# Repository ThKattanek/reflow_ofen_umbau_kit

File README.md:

# Reflow Ofen Umbau Kit
Mit dem „Reflow Ofen Umbau Kit“ (in Zukunft „Kit“ genannt) kann man einen alten Pizza Ofen zu einem Reflow Ofen umfunktionieren. Das Kit beinhaltet die komplette Mikrocontroller gestützte Steuerung und das entsprechende Netzteil welches die 5V und 12V bereitstellt. Dieses Kit ist für Hobbyelektroniker gedacht die hin und wieder eine Platine mit SMD Bauteilen löten wollen, jedoch eine Anschaffung eines Reflows Ofens zu kostenintensiv ist.

### [Letzte Offizelle Version findet ihr hier](https://github.com/ThKattanek/reflow_ofen_umbau_kit/releases/latest)

### YouTube Videos vom Projekt
|1.Teil|2.Teil|3.Teil|4.Teil|5.Teil|
|------|------|------|------|------|
|||||
### Hardware / Schaltplan
Die Hardware wurde mit KiCad entwickelt. Version 5.1.7 unter Ubuntu.

### PCB

### Verwendete Libs
LCD Ansteuerung von Mikrokontroller.net: http://www.mikrocontroller.net/articles/AVR-GCC-Tutorial/LCD-Ansteuerung

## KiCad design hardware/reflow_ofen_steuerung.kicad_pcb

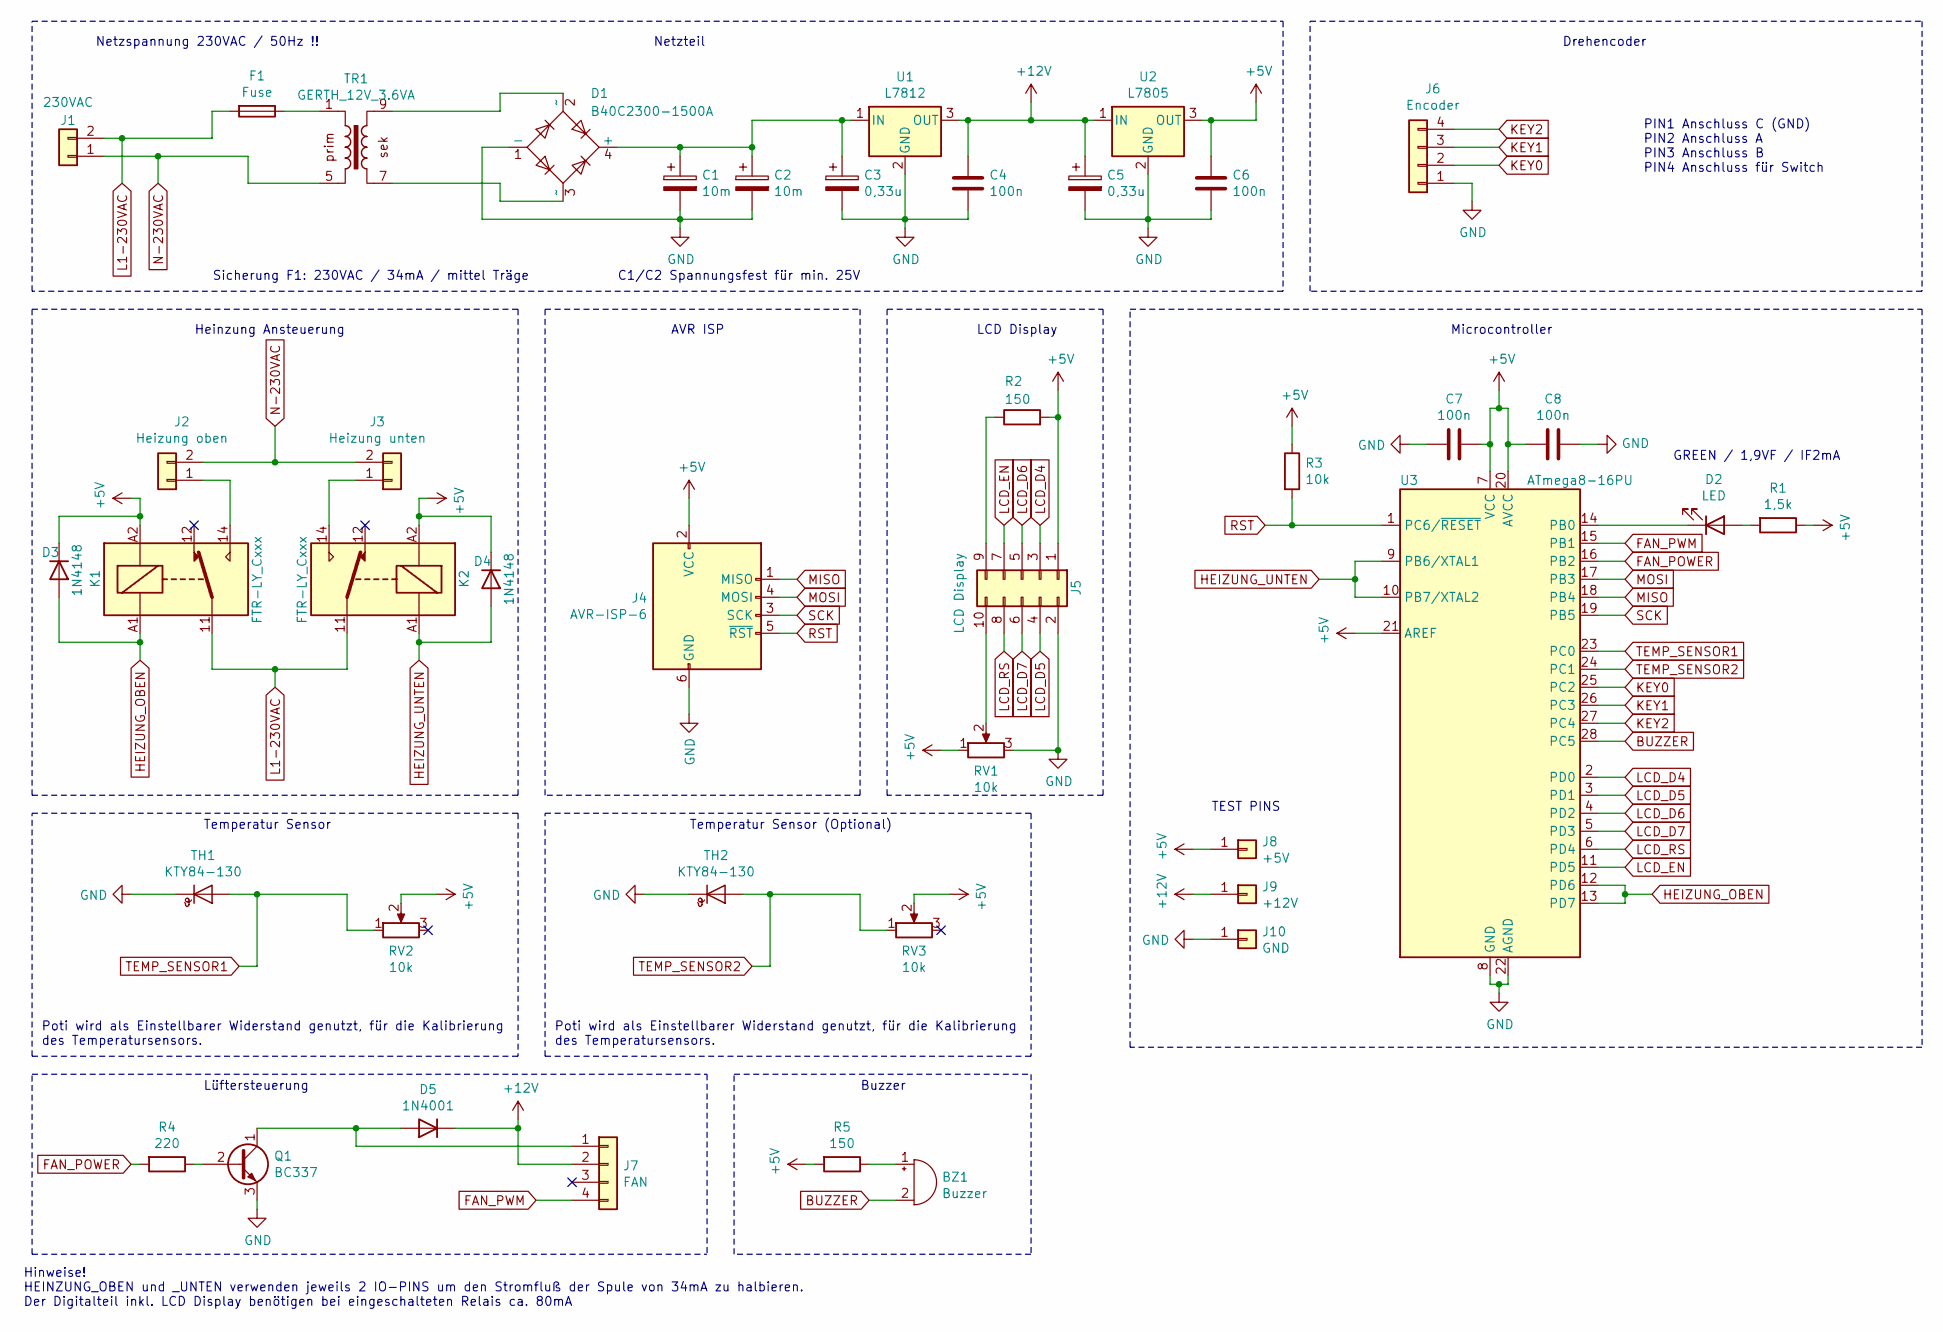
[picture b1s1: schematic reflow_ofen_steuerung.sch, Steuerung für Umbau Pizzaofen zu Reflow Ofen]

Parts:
BZ1: Buzzer; Buzzer_TDK_PS1240P02BT_D12.2mm_H6.5mm
C1, C2: 10m; CP_Radial_D18.0mm_P7.50mm
C3, C5: 0,33u; CP_Radial_D4.0mm_P1.50mm
C4, C6, C7, C8: 100n; C_Disc_D5.0mm_W2.5mm_P2.50mm
D1: B40C2300-1500A; Diode_Bridge_19.0x3.5x10.0mm_P5.0mm
D2: LED; LED_D5.0mm
D3, D4: 1N4148; D_DO-35_SOD27_P7.62mm_Horizontal
D5: 1N4001; D_DO-41_SOD81_P10.16mm_Horizontal
F1: Fuse; Fuseholder_Cylinder-6.3x32mm_Schurter_0031-8002_Horizontal_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
J1: 230VAC; TerminalBlock_RND_205-00287_1x02_P5.08mm_Horizontal
J2: Heizung oben; TerminalBlock_RND_205-00287_1x02_P5.08mm_Horizontal
J3: Heizung unten; TerminalBlock_RND_205-00287_1x02_P5.08mm_Horizontal
J4: AVR-ISP-6; IDC-Header_2x03_P2.54mm_Vertical
J5: LCD Display; IDC-Header_2x05_P2.54mm_Vertical
J6: Encoder; Molex_KK-254_AE-6410-04A_1x04_P2.54mm_Vertical
J7: FAN; Molex_KK-254_AE-6410-04A_1x04_P2.54mm_Vertical
J8: +5V; TestPoint_Bridge_Pitch2.0mm_Drill0.7mm
J9: +12V; TestPoint_Bridge_Pitch2.0mm_Drill0.7mm
J10: GND; TestPoint_Bridge_Pitch2.0mm_Drill0.7mm
K1, K2: FTR-LY_Cxxx
Q1: BC337; TO-92_Inline
R1: 1,5k; R_Axial_DIN0207_L6.3mm_D2.5mm_P7.62mm_Horizontal
R2, R5: 150; R_Axial_DIN0207_L6.3mm_D2.5mm_P7.62mm_Horizontal
R3: 10k; R_Axial_DIN0207_L6.3mm_D2.5mm_P7.62mm_Horizontal
R4: 220; R_Axial_DIN0207_L6.3mm_D2.5mm_P7.62mm_Horizontal
RV1, RV2, RV3: 10k; Potentiometer_Bourns_3296W_Vertical
TH1, TH2: KTY84-130; Molex_KK-254_AE-6410-02A_1x02_P2.54mm_Vertical
TR1: GERTH_12V_3.6VA; Transformer_NF_GERTH_387.12-1
U1: L7812; TO-220-3_Vertical
U2: L7805; TO-220-3_Vertical
U3: ATmega8-16PU; DIP-28_W7.62mm

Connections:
+5V: C6.1, C7.1, C8.2, D3.1 (K), D4.1 (K), J4.2 (VCC), J5.1, J8.1, K1.A2, K2.A2, R1.1, R2.2, R3.1, R5.2, RV1.1, RV2.2, RV3.2, U2.3 (OUT), U3.7 (VCC), U3.20 (AVCC), U3.21 (AREF)
+12V: C4.1, C5.1, D5.1 (K), J7.2, J9.1, U1.3 (OUT), U2.1 (IN)
BUZZER: BZ1.2 (+), U3.28 (PC5)
FAN_POWER: R4.2, U3.16 (PB2)
FAN_PWM: J7.4, U3.15 (PB1)
GND: C1.2, C2.2, C3.2, C4.2, C5.2, C6.2, C7.2, C8.1, D1.1 (-), J4.6 (GND), J5.2, J6.1, J10.1, Q1.3 (E), RV1.3, TH1.1 (K), TH2.1 (K), U1.2 (GND), U2.2 (GND), U3.8 (GND), U3.22 (AGND)
HEIZUNG_OBEN: D3.2 (A), K1.A1, U3.12 (PD6), U3.13 (PD7)
HEIZUNG_UNTEN: D4.2 (A), K2.A1, U3.9 (PB6/XTAL1), U3.10 (PB7/XTAL2)
KEY0: J6.2, U3.25 (PC2)
KEY1: J6.3, U3.26 (PC3)
KEY2: J6.4, U3.27 (PC4)
L1-230VAC: F1.2, J1.2, K1.11, K2.11
LCD_D4: J5.3, U3.2 (PD0)
LCD_D5: J5.4, U3.3 (PD1)
LCD_D6: J5.5, U3.4 (PD2)
LCD_D7: J5.6, U3.5 (PD3)
LCD_EN: J5.7, U3.11 (PD5)
LCD_RS: J5.8, U3.6 (PD4)
MISO: J4.1 (MISO), U3.18 (PB4)
MOSI: J4.4 (MOSI), U3.17 (PB3)
unnamed: J1.1, J2.2, J3.2, TR1.5
unnamed: BZ1.1 (-), R5.1
unnamed: C1.1, C2.1, C3.1, D1.4 (+), U1.1 (IN)
unnamed: D1.2 (~~), TR1.9
unnamed: D1.3 (~~), TR1.7
unnamed: D2.1 (K), U3.14 (PB0)
unnamed: D2.2 (A), R1.2
unnamed: D5.2 (A), J7.1, Q1.1 (C)
unnamed: F1.1, TR1.1
unnamed: J2.1, K1.14
unnamed: J3.1, K2.14
unnamed: J5.9, R2.1
unnamed: J5.10, RV1.2
unnamed: Q1.2 (B), R4.1
RST: J4.5 (~RST), R3.2, U3.1 (PC6/~RESET)
SCK: J4.3 (SCK), U3.19 (PB5)
TEMP_SENSOR1: RV2.1, TH1.2 (A), U3.23 (PC0)
TEMP_SENSOR2: RV3.1, TH2.2 (A), U3.24 (PC1)

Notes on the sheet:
Netzspannung 230VAC / 50Hz !!
C1/C2 Spannungsfest für min. 25V
Sicherung F1: 230VAC / 34mA / mittel Träge
Heinzung Ansteuerung
Netzteil
Microcontroller
GREEN / 1,9VF / IF2mA
LCD Display
AVR ISP
Hinweise! HEINZUNG_OBEN und _UNTEN verwenden jeweils 2 IO-PINS um den Stromfluß der Spule von 34mA zu halbieren. Der Digitalteil inkl. LCD Display benötigen bei eingeschalteten Relais ca. 80mA
Temperatur Sensor
Poti wird als Einstellbarer Widerstand genutzt, für die Kalibrierung des Temperatursensors.
Temperatur Sensor (Optional)
Drehencoder
PIN1 Anschluss C (GND) PIN2 Anschluss A PIN3 Anschluss B PIN4 Anschluss für Switch
Lüftersteuerung
Buzzer
TEST PINS

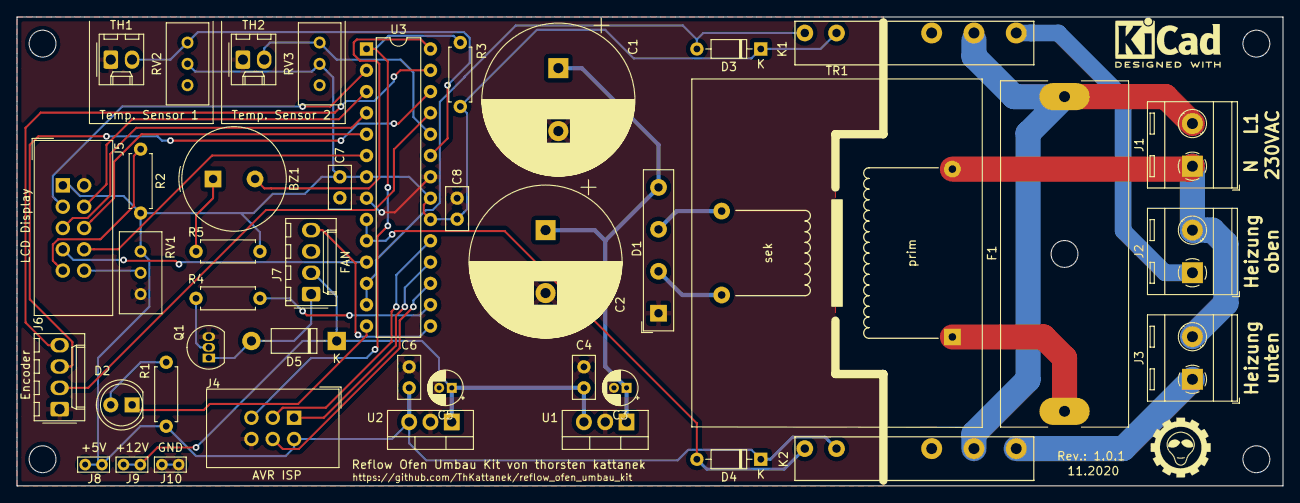
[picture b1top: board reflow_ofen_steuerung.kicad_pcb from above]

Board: 2 copper layers, 150.9 x 55.9 mm, 42 parts (0 on the bottom side), 38 nets.

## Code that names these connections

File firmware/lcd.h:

// Ansteuerung eines HD44780 kompatiblen LCD im 4-Bit-Interfacemodus
// http://www.mikrocontroller.net/articles/AVR-GCC-Tutorial/LCD-Ansteuerung
//
 
#ifndef LCD_ROUTINES_H
#define LCD_ROUTINES_H
 
////////////////////////////////////////////////////////////////////////////////
// Hier die verwendete Taktfrequenz in Hz eintragen, wichtig!
 
#ifndef F_CPU
#define F_CPU 4000000UL
#endif
 
////////////////////////////////////////////////////////////////////////////////
// Pinbelegung für das LCD, an verwendete Pins anpassen
// Alle LCD Pins müssen an einem Port angeschlossen sein und die 4
// Datenleitungen müssen auf aufeinanderfolgenden Pins liegen
 
//  LCD DB4-DB7 <-->  PORTD Bit PD0-PD3
#define LCD_PORT      PORTD
#define LCD_DDR       DDRD
#define LCD_DB        PD0
 
//  LCD RS      <-->  PORTD Bit PD4     (RS: 1=Data, 0=Command)
#define LCD_RS        PD4
 
//  LCD EN      <-->  PORTB Bit PB5     (EN: 1-Impuls für Daten)
#define LCD_EN        PD5
 
////////////////////////////////////////////////////////////////////////////////
// LCD Ausführungszeiten (MS=Millisekunden, US=Mikrosekunden)
 
#define LCD_BOOTUP_MS           15 	// 15
#define LCD_ENABLE_US           20	// 20
#define LCD_WRITEDATA_US        46	// 46
#define LCD_COMMAND_US          42	// 42
 
#define LCD_SOFT_RESET_MS1      5	// 5
#define LCD_SOFT_RESET_MS2      1	// 1
#define LCD_SOFT_RESET_MS3      1	// 1
#define LCD_SET_4BITMODE_MS     5	// 5
 
#define LCD_CLEAR_DISPLAY_MS    2	// 2	
#define LCD_CURSOR_HOME_MS      2	// 2
 
////////////////////////////////////////////////////////////////////////////////
// Zeilendefinitionen des verwendeten LCD
// Die Einträge hier sollten für ein LCD mit einer Zeilenlänge von 20 Zeichen passen
// Bei anderen Zeilenlängen müssen diese Einträge angepasst werden
 
#define LCD_DDADR_LINE1         0
#define LCD_DDADR_LINE2         64
#define LCD_DDADR_LINE3         20
#define LCD_DDADR_LINE4         84
 
////////////////////////////////////////////////////////////////////////////////
// Initialisierung: muss ganz am Anfang des Programms aufgerufen werden.
void lcd_init( void );
 
////////////////////////////////////////////////////////////////////////////////
// LCD löschen
void lcd_clear( void );
 
////////////////////////////////////////////////////////////////////////////////
// Cursor in die 1. Zeile, 0-te Spalte
void lcd_home( void );
 
////////////////////////////////////////////////////////////////////////////////
// Cursor an eine beliebige Position 
void lcd_setcursor( uint8_t spalte, uint8_t zeile );
 
////////////////////////////////////////////////////////////////////////////////
// Ausgabe eines einzelnen Zeichens an der aktuellen Cursorposition 
void lcd_data( uint8_t data );
 
////////////////////////////////////////////////////////////////////////////////
// Ausgabe eines Strings an der aktuellen Cursorposition 
void lcd_string( const char *data );
 
////////////////////////////////////////////////////////////////////////////////
// Schreibt einen String auf das LCD mit erweiterten Parametern
// start:   Position des erstes Zeichens im String was ausgegeben werden soll
// length:  Maximale Anzahl der Zeichen die Ausgegeben werden sollen
void lcd_print(char *string, uint8_t start, uint8_t length);

////////////////////////////////////////////////////////////////////////////////
// Definition eines benutzerdefinierten Sonderzeichens.
// data muss auf ein Array[8] mit den Zeilencodes des zu definierenden Zeichens
// zeigen
void lcd_generatechar( uint8_t code, const uint8_t *data );
 
////////////////////////////////////////////////////////////////////////////////
// Ausgabe eines Kommandos an das LCD.
void lcd_command( uint8_t data );
 
 
////////////////////////////////////////////////////////////////////////////////
// LCD Befehle und Argumente.
// Zur Verwendung in lcd_command
 
// Clear Display -------------- 0b00000001
#define LCD_CLEAR_DISPLAY       0x01
 
// Cursor Home ---------------- 0b0000001x
#define LCD_CURSOR_HOME         0x02
 
// Set Entry Mode ------------- 0b000001xx
#define LCD_SET_ENTRY           0x04
 
#define LCD_ENTRY_DECREASE      0x00
#define LCD_ENTRY_INCREASE      0x02
#define LCD_ENTRY_NOSHIFT       0x00
#define LCD_ENTRY_SHIFT         0x01
 
// Set Display ---------------- 0b00001xxx
#define LCD_SET_DISPLAY         0x08
 
#define LCD_DISPLAY_OFF         0x00
#define LCD_DISPLAY_ON          0x04
#define LCD_CURSOR_OFF          0x00
#define LCD_CURSOR_ON           0x02
#define LCD_BLINKING_OFF        0x00
#define LCD_BLINKING_ON         0x01
 
// Set Shift ------------------ 0b0001xxxx
#define LCD_SET_SHIFT           0x10
 
#define LCD_CURSOR_MOVE         0x00
#define LCD_DISPLAY_SHIFT       0x08
#define LCD_SHIFT_LEFT          0x00
#define LCD_SHIFT_RIGHT         0x04
 
// Set Function --------------- 0b001xxxxx
#define LCD_SET_FUNCTION        0x20
 
#define LCD_FUNCTION_4BIT       0x00
#define LCD_FUNCTION_8BIT       0x10
#define LCD_FUNCTION_1LINE      0x00
#define LCD_FUNCTION_2LINE      0x08
#define LCD_FUNCTION_5X7        0x00
#define LCD_FUNCTION_5X10       0x04
 
#define LCD_SOFT_RESET          0x30
 
// Set CG RAM Address --------- 0b01xxxxxx  (Character Generator RAM)
#define LCD_SET_CGADR           0x40
 
#define LCD_GC_CHAR0            0
#define LCD_GC_CHAR1            1
#define LCD_GC_CHAR2            2
#define LCD_GC_CHAR3            3
#define LCD_GC_CHAR4            4
#define LCD_GC_CHAR5            5
#define LCD_GC_CHAR6            6
#define LCD_GC_CHAR7            7
 
// Set DD RAM Address --------- 0b1xxxxxxx  (Display Data RAM)
#define LCD_SET_DDADR           0x80
 
#endif 

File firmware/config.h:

/* Name: config.h
 * Projekt: reflow_ofen_steuerung
 * Author: Thorsten Kattanek
 * Geändert am: 27.09.2020
 * Copyright: Thorsten Kattanek
 * License: GNU GPL v2 (see License.txt), GNU GPL v3 or proprietary (CommercialLicense.txt)
 *
 */ 

// Konfiguration /////////////////////////////////////////////////

// LCD
#define LCD_LINE_COUNT 4
#define LCD_LINE_SIZE 20

// Zeit in ms wie lange die Version nach dem Start angezeigt wird
#define START_MESSAGE_TIME 1500

// Status LED Cofiguration --> PortB Pin0
#define STATUS_LED_PORT     PORTB
#define STATUS_LED_DDR      DDRB
#define STATUS_LED_PIN      PIN0

// Einabetasten
#define KEY0_DDR DDRC
#define KEY0_PORT PORTC
#define KEY0_PIN PINC
#define KEY0	 PINC3

#define KEY1_DDR DDRC
#define KEY1_PORT PORTC
#define KEY1_PIN PINC
#define KEY1	 PINC2

#define KEY2_DDR DDRC
#define KEY2_PORT PORTC
#define KEY2_PIN PINC
#define KEY2	 PINC4

#define get_key0() (~KEY0_PIN & (1<<KEY0))
#define get_key1() (~KEY1_PIN & (1<<KEY1))
#define get_key2() (~KEY2_PIN & (1<<KEY2))


#define IMPULS_1A_PIN KEY1
#define IMPULS_1A_PORT KEY1_PORT
#define IMPULS_1A_DDR KEY1_DDR

#define IMPULS_1B_PIN KEY0
#define IMPULS_1B_PORT KEY0_PORT
#define IMPULS_1B_DDR KEY0_DDR

// Heizungsteuerung
// Heizung unten
#define HEATING_BOTTOM_PORT   PORTB
#define HEATING_BOTTOM_DDR    DDRB
#define HEATING_BOTTOM_PIN    PIN6

// Heizung oben
#define HEATING_TOP_PORT   PORTD
#define HEATING_TOP_DDR    DDRD
#define HEATING_TOP_PIN    PIN6

// Buzzer (Dauerton)
#define BUZZER_PORT     PORTC
#define BUZZER_DDR      DDRC
#define BUZZER_PIN      PIN5

// Motor Power
#define MOTOR_POWER_PORT     PORTB
#define MOTOR_POWER_DDR      DDRB
#define MOTOR_POWER_PIN      PIN2

// Temperatur Sensor 1
#define SENSOR1_PORT    PORTC
#define SENSOR1_DDR     DDRC
#define SENSOR1_PIN     PIN0

// Temperatur Sensor 2 (Optional)
#define SENSOR2_PORT    PORTC
#define SENSOR2_DDR     DDRC
#define SENSOR2_PIN     PIN1

/////////////////////////////////////////////////////////////////////////////////////////////

#define status_led_init() STATUS_LED_DDR |= 1 << STATUS_LED_PIN; STATUS_LED_PORT |= 1 << STATUS_LED_PIN
#define status_led_on() STATUS_LED_PORT &= ~(1 << STATUS_LED_PIN)
#define status_led_off() STATUS_LED_PORT |= 1 << STATUS_LED_PIN

#define heating_bottom_init() HEATING_BOTTOM_DDR |= 0x03 << HEATING_BOTTOM_PIN; HEATING_BOTTOM_PORT |= 0x03 << HEATING_BOTTOM_PIN
#define heating_top_init() HEATING_TOP_DDR |= 0x03 << HEATING_TOP_PIN; HEATING_TOP_PORT |= 0x03 << HEATING_TOP_PIN

#define heating_bottom_on() HEATING_BOTTOM_PORT &= ~(0x03 << HEATING_BOTTOM_PIN)
#define heating_top_on() HEATING_TOP_PORT &= ~(0x03 << HEATING_TOP_PIN)

#define heating_bottom_off() HEATING_BOTTOM_PORT |= 0x03 << HEATING_BOTTOM_PIN
#define heating_top_off() HEATING_TOP_PORT |= 0x03 << HEATING_TOP_PIN

#define buzzer_init() BUZZER_DDR |= 0x03 << BUZZER_PIN; BUZZER_PORT |= 0x03 << BUZZER_PIN
#define buzzer_on() BUZZER_PORT &= ~(0x03 << BUZZER_PIN)
#define buzzer_off() BUZZER_PORT |= 0x03 << BUZZER_PIN

#define motor_power_init() MOTOR_POWER_DDR |= 1 << MOTOR_POWER_PIN
#define motor_power_on() MOTOR_POWER_PORT |= 1 << MOTOR_POWER_PIN
#define motor_power_off() MOTOR_POWER_PORT &= ~(1 << MOTOR_POWER_PIN)

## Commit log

2020-10-03 changed README.md
2020-10-07 PCB angepasst für Kühlkörper der Spannungsregler
2020-10-14 changed screenshots from 3d pcb
2020-10-22 added 150 ohm resistor for buzzer
2020-10-22 added buzzer in config.h and main.c
2020-10-23 added gerber files
2020-10-23 changed .gitignore
2020-10-23 added 3d fuse model in fuse holder footprint
2020-10-23 changed .gitignore -> added qt creator files
2020-10-24 changed label ADC0/1 to TEMP_SENSOR1/2
2020-10-27 changed firmware: added fan control
2020-10-27 changed firmware: test fanspeed with temperature sensor
2020-11-18 added bom
2020-11-20 Brückengleichrichter D1 korrigiert
2021-01-16 firmware: added menu und first soldering program
2021-01-24 firmware: added temper function
